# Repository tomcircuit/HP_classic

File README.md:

# HP_classic - LiPo Battery for HP 'Classic' Calculators - Version 2
 
This is my attempt at a LiPo-based battery pack for "Classic" HP Calculators, specifically HP-35, HP-45, and HP-55.  The original NiCd packs are all dead by now, and rebuilding them is difficult - *assuming you can even find a pack to rebuild*. I thought it would be fun to use a rechargeable LiPo battery, and include the circuitry to re-charge via USB as well. 

> LiPo chemistry has very specific care-and-feeding when it comes to recharging, **you cannot use the HP AC charger to recharge this pack!**  Don't even try it with Version 1 of this project!

**UPDATE**: Version 2 design includes *Charger Immunity* circuitry to prevent mayhem if the HP AC  charger is connected. 

The basic idea is to use a gold-flashed (ENIG) PCB as the contact substrate, and mount the LiPo, USB micro B receptacle, and charging circuitry on the opposite side. The 'charger immunity' introduced in Version 2 is placed on the same side as the contact pads, but in areas where there will be no mechanical interference. A pair of laser-cut 'endcaps' locate the assembly within the battery well and allow the compartment cover to hold it in place. 

## The Endcaps
I just happen to have an original NiCd HP battery pack, so I was able to measure its end profile and draw it in MS Visio and export as an SVG file. The endcap is laser-cut from 3mm thick fiberboard and its overall size is **47mm x  14mm**. I'm sure you could use some other material if you desired. I went with fiberboard in case I needed to tweak it, and because it is cheap. Two endcaps are required for each pack. 

I had a batch of 6 pcs made by [Ponoko](https://www.ponoko.com/) and they were very inexpensive, less than $1 each. Consider that Ponoko has a flat $14 setup charge per design, however. If you have other means to access a laser cutter, you can probably do this much more cheaply.

## The PCB 
The PCB holds the USB micro B connector, the charging circuitry, the protection circuitry, a connector for the LiPo battery, and most importantly the pads that mate with the contacts in the calculator.  The overall size of the PCB is 56mm x 40mm. The material is 1.6mm thick FR4. So that the contact pads do not  tarnish over time, I chose a gold-flash treatment (ENIG). 

The schematic and PCB were designed using KiCAD. Note that the PCB can accommodate either a JST or 0.1" two pin battery connector type.

I had the V1 PCB fabricated by [PCBWay](https://www.pcbway.com/)  This was the second PCB that I've had made by them, and I am once again very satisfied with the speed, quality, and price. The PCB can be ordered from them directly as a [shared project](https://www.pcbway.com/project/shareproject/HP_Classic_Calculator_LiPo_Battery_Pack.html). 

UPDATE: I will have the V2 PCB fabricated there, as well, and include a link when it's available.

## The LiPo Battery
I wanted a 1S (3.7V) LiPo battery in the neighborhood of 1000mAhr that would fit within the confines of the original pack envelope. This led me to a size "803040" LiPo battery. I prefer the JST connector, so I found one with that connector type. The PCB can accommodate either JST or "two pin" connectors, so there's some flexibility here. 

I believe that a thicker battery could be used, because of the profile of the battery compartment cover. That might allow for a higher capacity battery, which would translate into longer running time. 

**UPDATE**: I founda  1200mAhr LiPo battery in size "103040" that is just 2mm thicker. I've ordered some to try out.  20% more capacity is always good, right?

## Putting It All Together
Pretty self-explanatory. I used 0805 size components to allow for easy hand-soldering. Note that D1 is an LED and is polarized, so pay attention to that. Soldering the USB connector requires a fine-tip iron and some patience. 

The endcaps each need a small amount of Krazy glue to keep them in place, and the PCB edges should be flush with the outer surface of each endcap to match the overall size of the original battery pack.
> You will not be able to access the USB connector's solder joints after the endcap is installed, so be sure of your workmanship there before you glue that particular endcap in place

**UPDATE**: I've rotated the USB connector 180degrees on PCB V2, so that the solder joints can be accessed even after the endcap is glued on. It's still a good idea to wait until everything is tested before gluing on the endcaps, though.

I don't know if there are 'standards' for LiPo battery connector polarity, but I managed to get a battery that had the opposite pinning than what I expected. I had to swap the polarity of the battery plug to make it match PCB V1 pinout. Plug the battery in and tape it to the PCB. 

**UPDATE**: I've swapped the JST connector pins on PCB V2 so that they agree with all of the LiPo batteries that I could find photos of on the web.  This should make life easier for everyone in the future.

## Charge It
Connect a micro-B cable to the board and charge the LiPo battery. The LED will stay lit during the charging process, and extinguish when it is completed. The charge current is about 200mA (0.2C for a 1000mAhr battery). You can adjust R1 to change the current if you need to. It took about two hours to charge my battery,

## Use It!
Install the pack into the calculator, paying attention to mate the contact pads with the contacts in the calculator. The pads are sized to prevent contact if the pack is inserted incorrectly, but I do not recommend testing to find out if I got that all right or not. My understanding is that these classic calculators will not withstand reverse voltage. Don't risk it.

If you've done everything correctly, you should be greeted with 0.00 when you turn your calculator on. Your classic calculator is now sipping power from a modern, convenient, and most importantly *non-leaking* battery pack.  Enjoy!

December 2, 2020
Tom LeMense
rev 2
<!--stackedit_data:
eyJoaXN0b3J5IjpbLTIzMjk3MDczOF19
-->

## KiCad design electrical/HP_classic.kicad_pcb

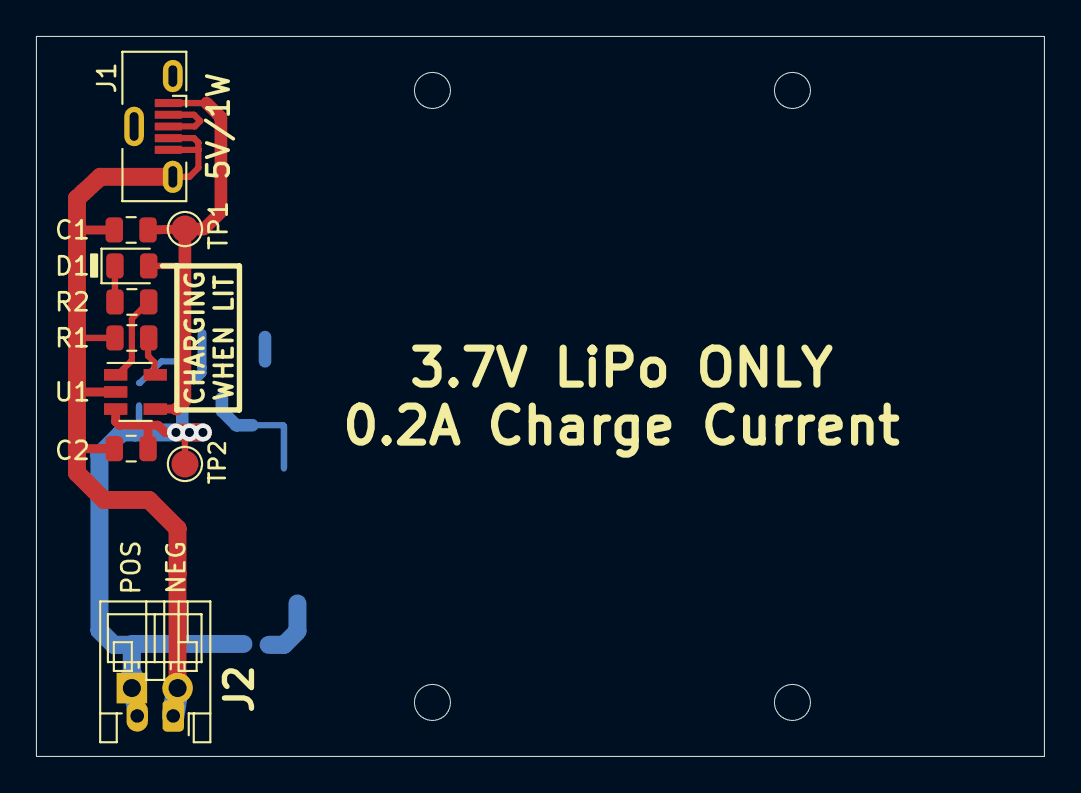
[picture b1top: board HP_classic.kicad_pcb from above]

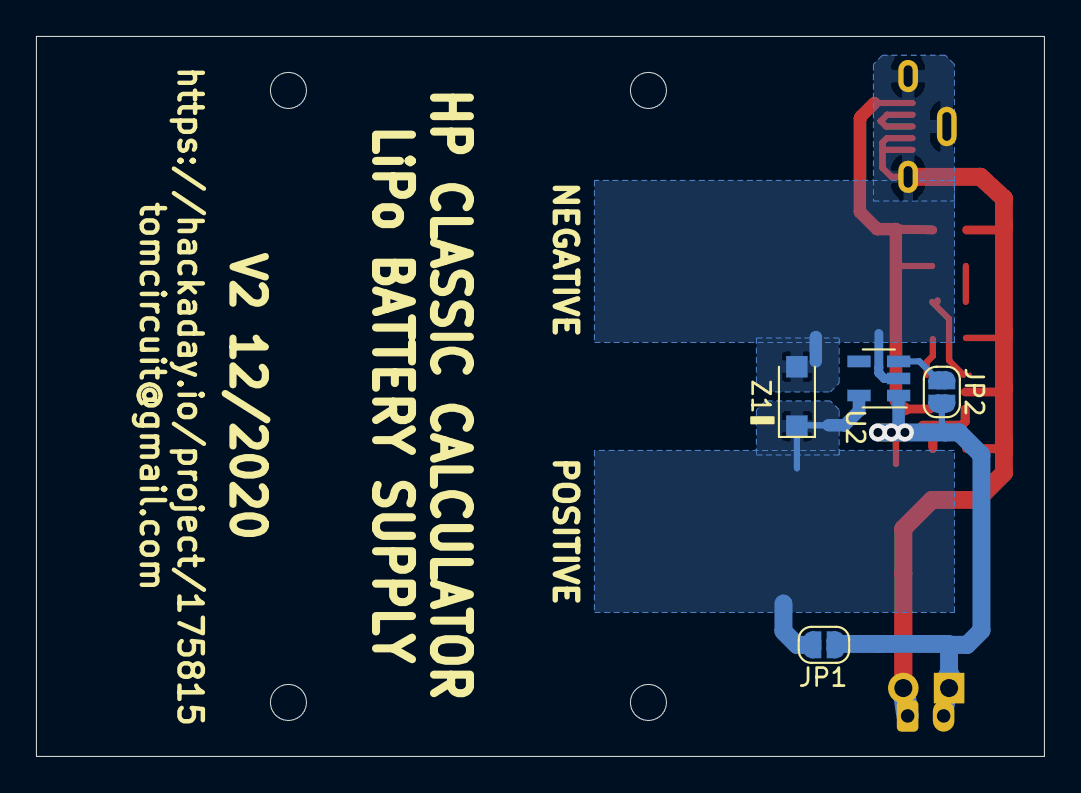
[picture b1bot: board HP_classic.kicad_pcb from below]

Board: 2 copper layers, 56.0 x 40.0 mm, 19 parts (4 on the bottom side), 9 nets.

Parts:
C1, C2: 4.7uF; C_0805_2012Metric
D1: LED; LED_0805_2012Metric
H1, H2, H3, H4: MountingHole; MountingHole_2mm
J1: USB_B_Micro; USB_Micro-B_Molex-105133-0001
J2: JST PH 2mm; JST_PH_S2B-PH-K_1x02_P2.00mm_Horizontal
J3: 2.54mm R/A; PinHeader_1x02_P2.54mm_Horizontal
JP1: BYPASS; SolderJumper-2_P1.3mm_Open_RoundedPad1.0x1.5mm
JP2: ENABLE; SolderJumper-2_P1.3mm_Open_RoundedPad1.0x1.5mm
R1: 4.7K; R_0805_2012Metric
R2: 470; R_0805_2012Metric
TP1: VUSB; TestPoint_Pad_D1.5mm
TP2: VBAT; TestPoint_Pad_D1.5mm
U1: MCP73831-2-OT; SOT-23-5
U2: MAX40203AUK; SOT-23-5
Z1: MMBZ5231; D_SOD-123

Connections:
/POS: JP1.2, U2.5, Z1.1
/VBAT: C2.1, J2.2, J3.1, JP1.1, JP2.1, TP2.1, U1.3, U2.1
/VUSB: C1.1, D1.2, J1.1, TP1.1, U1.4
GND: C1.2, C2.2, J1.4, J1.5, J1.6, J2.1, J3.2, R1.2, U1.2, U2.2, Z1.2
unnamed: D1.1, R2.2
unnamed: J1.2, J1.3
unnamed: JP2.2, U2.3
unnamed: R1.1, U1.5
unnamed: R2.1, U1.1

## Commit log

2020-11-11 Update README.md
    added info to README file
2020-11-18 Version 1 Checkin
    Schematic updated with component details
    PCB udpated for plot formatting
    Check plots generated
    Interactive BOM generated
2020-11-18 Updated readme file
2020-11-18 Rev 1 release
    bumped rev to 1 on schematic. generated PDF schematic file.
2020-11-25 Added simulation on MAX40203 ideal diode
    Simuation in LTspice on MAX40203 'ideal diode' reverse current protection for LiPo cell when HP AC adapter is connected. This will prevent the HP charger from attempting to 'trickle charge' the LiPo 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
2020-12-02 upload version 2 ecad and updates
    Upload of v2 KiCad schematic, PCB, and BOM information. V2 includes protection circuitry to prevent damage if an HP charger is attached while this pack is installed in the calculator.
2020-12-02 Updated readme.MD file
    Updated the readme file with V2 specifics.
2020-12-02 typo in readme.MD
2020-12-02 readme.md created from https://stackedit.io/
2021-01-24 added photos of V2 board
2021-01-25 Corrected note on schematic
    Note describing Zener Z1 referred to D2. There is no D2, only Z1.
